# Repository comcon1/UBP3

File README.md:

# Universal Biopotential Amplifier - UBP3

Wideband multichannel differential amplifier with modular design and adjustable analogous commutation.

## Project video

## Technical characteristics

- Input power: -15, 0, +15 V
- Type: differential
- Input resistance: 1 GOhm
- Noise level at connected inputs:
  - < 0.15 mkV (at 0.3-150 Hz)
  - < 0.8 mkV (at 0.3-1000 Hz)
- Gain coefficient:
  - Input cascade: 1, 10
  - Output cascade: 3, 10, 30, 100, 300, 1000
- Filtering:
  - Intensity: 12 dB/octave
  - LowPass: 35, 70, 150, 300, 1000, 2000, 5000, 10000, 20000 Hz 
  - HighPass: 0.1, 0.3, 1, 5, 20, 100, 300 Hz
- Output range: -5V - +5V

# Project structure

The amplifier is composed of two boards: **InputAmp** and **FilterAmp**. 

## InputAmp

Input gain board performs initial commutation of the bipolar signal with reference monopolar input and calibration signal. Next the board amplifies the signal current with 1x/10x gain.

Corresponding directory contains the complete KiCAD project including scheme and PCB.

## FilterAmp

Preamplified signal is then further amplified inside this board and undergo LowPass and HighPass filtration.

Corresponding directory contains the complete KiCAD project including scheme and PCB.

## Calibrator

Calibrator gets 0/+5V input unipolar source and gives 30/300 Hz of 1/0.1 mV square pulse unipolar signal for feeding the amplifier.

Corresponding directory contains the complete KiCAD project including scheme and PCB.

# Arrangement

Boards are designed for further geometrical stacking as shown at the how-to-assembly scheme:

# History

The prototype of this amplifier was firstly used by Ilya Kuzmin and colleagues for recording ECG of rats on a tredban:

- Tarasova OS, Borzykh AA, Kuz'min IV, et al. [Dynamics of heart rate changes in rats following stepwise change of treadmill running speed]. Ross Fiziol Zh Im I M Sechenova. 2012; 98(11):1372-9.

Now it is used by Georgy Nikolaev and his students for recording EEG in the research of audiogenic epilepsy on rat model:

- Fedotova IB, Surina NM, Nikolaev GM, Revishchin AV, Poletaeva II. Rodent Brain Pathology, Audiogenic Epilepsy. Biomedicines. 2021; 9(11):1641. https://doi.org/10.3390/biomedicines9111641

# Licensing 

The project "Universal Biopotential Amplifier" 
(I. Kuzmin @kuzmin-ilya, A. Nesterenko @comcon1, G. Nikolaev)  
is released under  license CC BY-SA 3.0.

Submodules listed as independent projects are not part of this project and 
are released under their own licenses.

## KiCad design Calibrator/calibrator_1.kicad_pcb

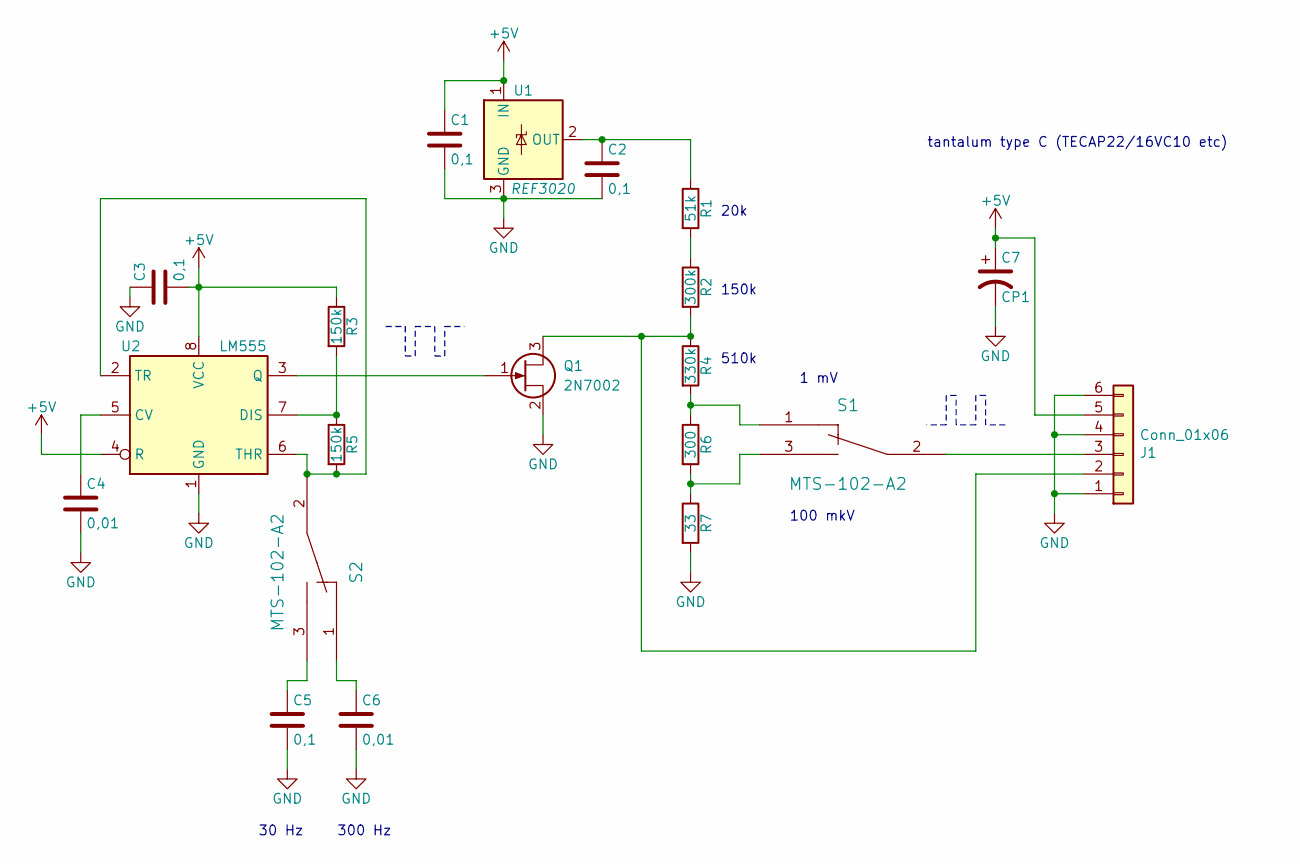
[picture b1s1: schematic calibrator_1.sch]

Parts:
C1, C2, C3, C5: 0,1; C_0805_2012Metric_Pad1.15x1.40mm_HandSolder
C4, C6: 0,01; C_0805_2012Metric_Pad1.15x1.40mm_HandSolder
C7: CP1; CP_EIA-6032-28_Kemet-C_Pad2.25x2.35mm_HandSolder
J1: Conn_01x06; PinHeader_1x06_P2.54mm_Horizontal
Q1: 2N7002; SOT-23_Handsoldering
R1: 51k; R_0805_2012Metric_Pad1.15x1.40mm_HandSolder
R2: 300k; R_0805_2012Metric_Pad1.15x1.40mm_HandSolder
R3, R5: 150k; R_0805_2012Metric_Pad1.15x1.40mm_HandSolder
R4: 330k; R_0805_2012Metric_Pad1.15x1.40mm_HandSolder
R6: 300; R_0805_2012Metric_Pad1.15x1.40mm_HandSolder
R7: 33; R_0805_2012Metric_Pad1.15x1.40mm_HandSolder
S1, S2: MTS-102-A2
U1: REF3020; SOT-23_Handsoldering
U2: LM555; SOIC-8_3.9x4.9mm_P1.27mm

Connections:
+5V: C1.1, C3.2, C7.1, J1.5, R3.1, U1.1 (IN), U2.4 (R), U2.8 (VCC)
GND: C1.2, C2.2, C3.1, C4.2, C5.2, C6.2, C7.2, J1.1, J1.4, J1.6, Q1.2 (S), R7.2, U1.3 (GND), U2.1 (GND)
unnamed: C2.1, R1.1, U1.2 (OUT)
unnamed: C4.1, U2.5 (CV)
unnamed: C5.1, S2.3
unnamed: C6.1, S2.1
unnamed: J1.2, Q1.3 (D), R2.2, R4.1
unnamed: J1.3, S1.2
unnamed: Q1.1 (G), U2.3 (Q)
unnamed: R1.2, R2.1
unnamed: R3.2, R5.1, U2.7 (DIS)
unnamed: R4.2, R6.1, S1.1
unnamed: R5.2, S2.2, U2.2 (TR), U2.6 (THR)
unnamed: R6.2, R7.1, S1.3

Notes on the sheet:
30 Hz
300 Hz
1 mV
100 mkV
tantalum type C (TECAP22/16VC10 etc)
510k
150k
20k

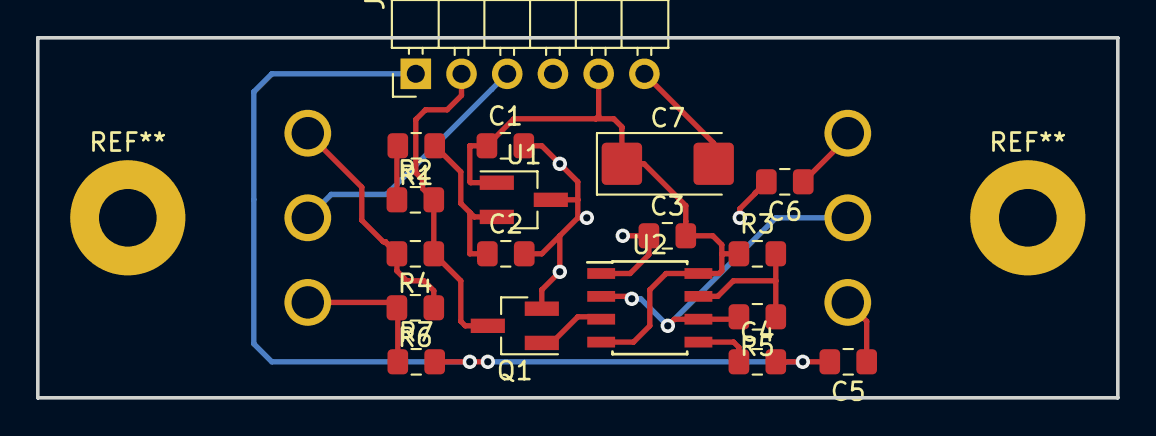
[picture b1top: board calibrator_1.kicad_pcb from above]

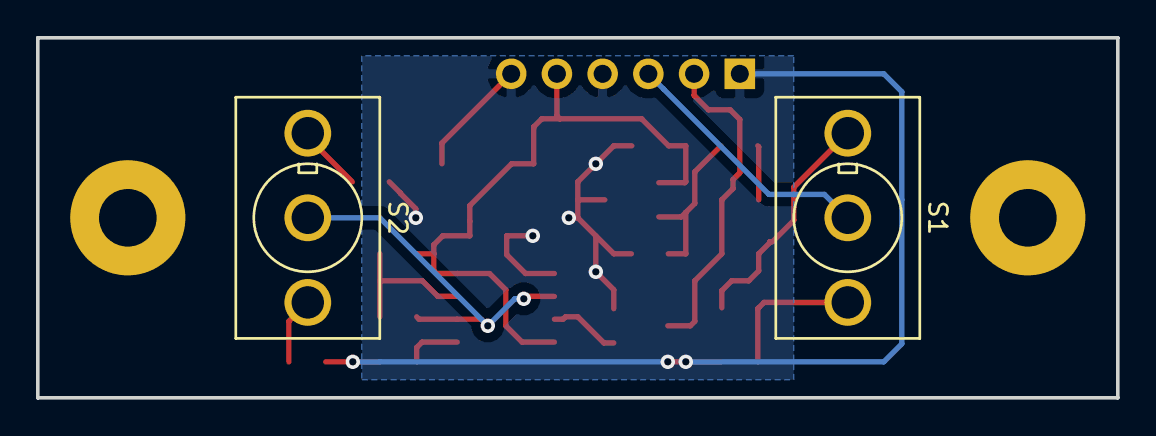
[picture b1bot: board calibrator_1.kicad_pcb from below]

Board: 2 copper layers, 60.0 x 20.0 mm, 20 parts (2 on the bottom side), 14 nets.

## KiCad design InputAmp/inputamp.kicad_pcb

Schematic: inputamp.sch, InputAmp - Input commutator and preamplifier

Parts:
C1, C2, C5: 1,0; C_Rect_L7.5mm_W6.5mm_P5.00mm
C3, C4: 0,1; C_0805_2012Metric_Pad1.18x1.45mm_HandSolder
J1: Conn_01x04; PinHeader_1x04_P2.54mm_Vertical
J2: Conn_01x03; PhoenixContact_MCV_1,5_3-G-3.81_1x03_P3.81mm_Vertical
J3, J5: Conn_01x04; SolderWirePad_1x04_P3.81mm_Drill1.2mm
J4: Conn_01x03; SolderWirePad_1x03_P3.81mm_Drill1.2mm
R1, R2: 20M; R_Axial_DIN0309_L9.0mm_D3.2mm_P12.70mm_Horizontal
R3: 7,5k; R_0805_2012Metric_Pad1.20x1.40mm_HandSolder
R4, R5, R6, R7, R8, R9: 30k; R_0805_2012Metric_Pad1.20x1.40mm_HandSolder
R10: 2M; R_0805_2012Metric_Pad1.20x1.40mm_HandSolder
R11: 33k; R_0805_2012Metric_Pad1.20x1.40mm_HandSolder
R12: 300k; R_0805_2012Metric_Pad1.20x1.40mm_HandSolder
SW1, SW2: MTS-202-A2; MTS-202-A2_odd_even
SW3, SW5, SW6: MTS-102-A2
SW4, SW7: MTS-212-A2; MTS-202-A2_odd_even
U1: TLC2274; SOIC-14_3.9x8.7mm_P1.27mm

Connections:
+5V: C3.2, J1.1, J4.1, U1.4
-5V: C4.2, J1.2, J4.3, U1.11
GND: C3.1, C4.1, J1.4, J2.2, J3.2, J4.2, J5.2, R1.2, R2.2, R8.2, R10.2, R11.2, SW1.5 (C), SW4.5 (C), SW7.6 (C)
unnamed: C1.1, R1.1, SW2.3 (B), U1.3
unnamed: C1.2, SW1.3 (B), SW2.1 (A)
unnamed: C2.1, R2.1, SW2.4 (B), U1.5
unnamed: C2.2, SW1.4 (B), SW2.2 (A)
unnamed: C5.1, R10.1, U1.12
unnamed: C5.2, R9.1, SW3.1, U1.8
unnamed: J1.3, SW3.2
unnamed: J2.1, SW7.2 (A)
unnamed: J2.3, SW4.1 (A)
unnamed: J3.1, J5.1, SW5.3, SW6.3
unnamed: J3.3, J5.3, SW1.6 (C)
unnamed: J3.4, J5.4, SW4.4 (B), SW7.3 (B)
unnamed: R3.1, R4.2, U1.2
unnamed: R3.2, R5.2, U1.6
unnamed: R4.1, R6.2, U1.1
unnamed: R5.1, R7.2, U1.7
unnamed: R6.1, R9.2, U1.9
unnamed: R7.1, R8.1, U1.10
unnamed: R11.1, R12.2, U1.13
unnamed: R12.1, SW3.3, U1.14
unnamed: SW1.1 (A), SW5.2
unnamed: SW1.2 (A), SW6.2
unnamed: SW4.3 (B), SW6.1, SW7.5 (C)
unnamed: SW4.6 (C), SW5.1, SW7.4 (B)

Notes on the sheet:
x10
CAL
ShieldGND
C1, C2, C5 - Epcos B32529C0105K000
Output connector (to "filteramp" block)
Reserve connector to supply power for input devices
Signal input connector
IN- GND IN+
LowPass frequency is about 0.1 Hz
SIG_OUT GND
REF
Rin
CAL_R
"CAL_R": to the +1V output of the calibrator through 1 MOhm "CAL": directly to the +1mV output of the calibrator "REF": when the circuite works in a stack, one of the inputs (called REF) is connected to all boards and may replace + or - inputs "ShieldGND": connect the shield of REF wire and DON'T c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
Connect to J5 of the next board in a stack. DON'T connect ShieldGND between boards!

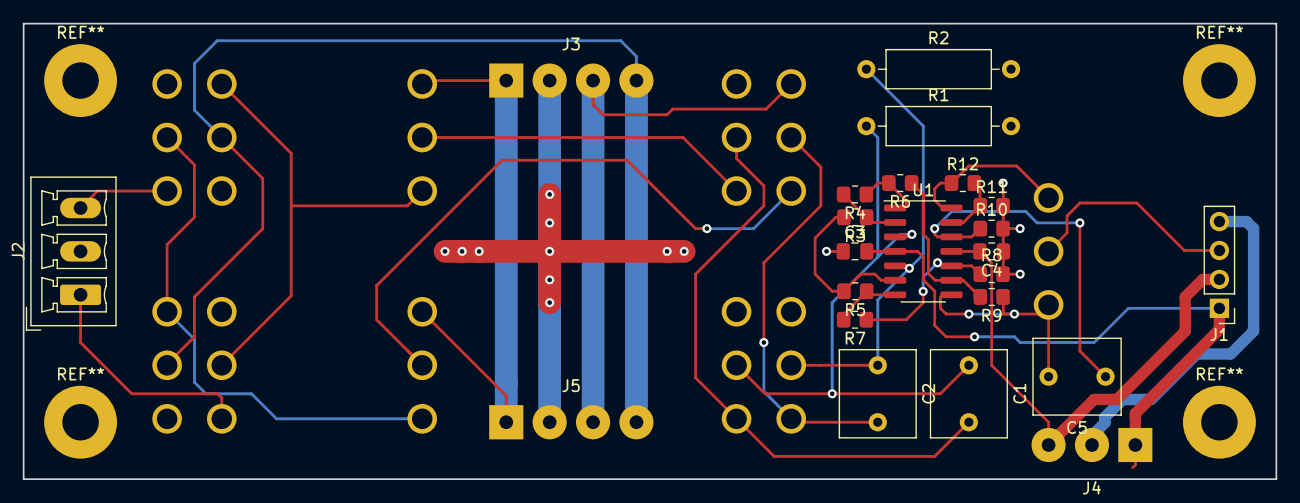
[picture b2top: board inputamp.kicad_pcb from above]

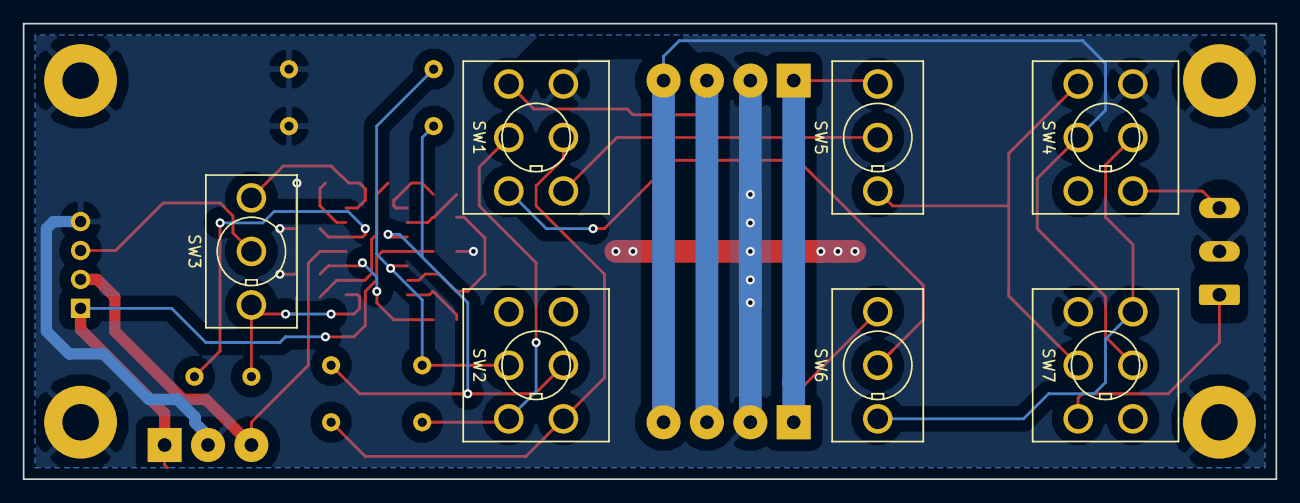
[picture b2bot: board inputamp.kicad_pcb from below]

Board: 2 copper layers, 110.0 x 40.0 mm, 30 parts (7 on the bottom side), 27 nets.

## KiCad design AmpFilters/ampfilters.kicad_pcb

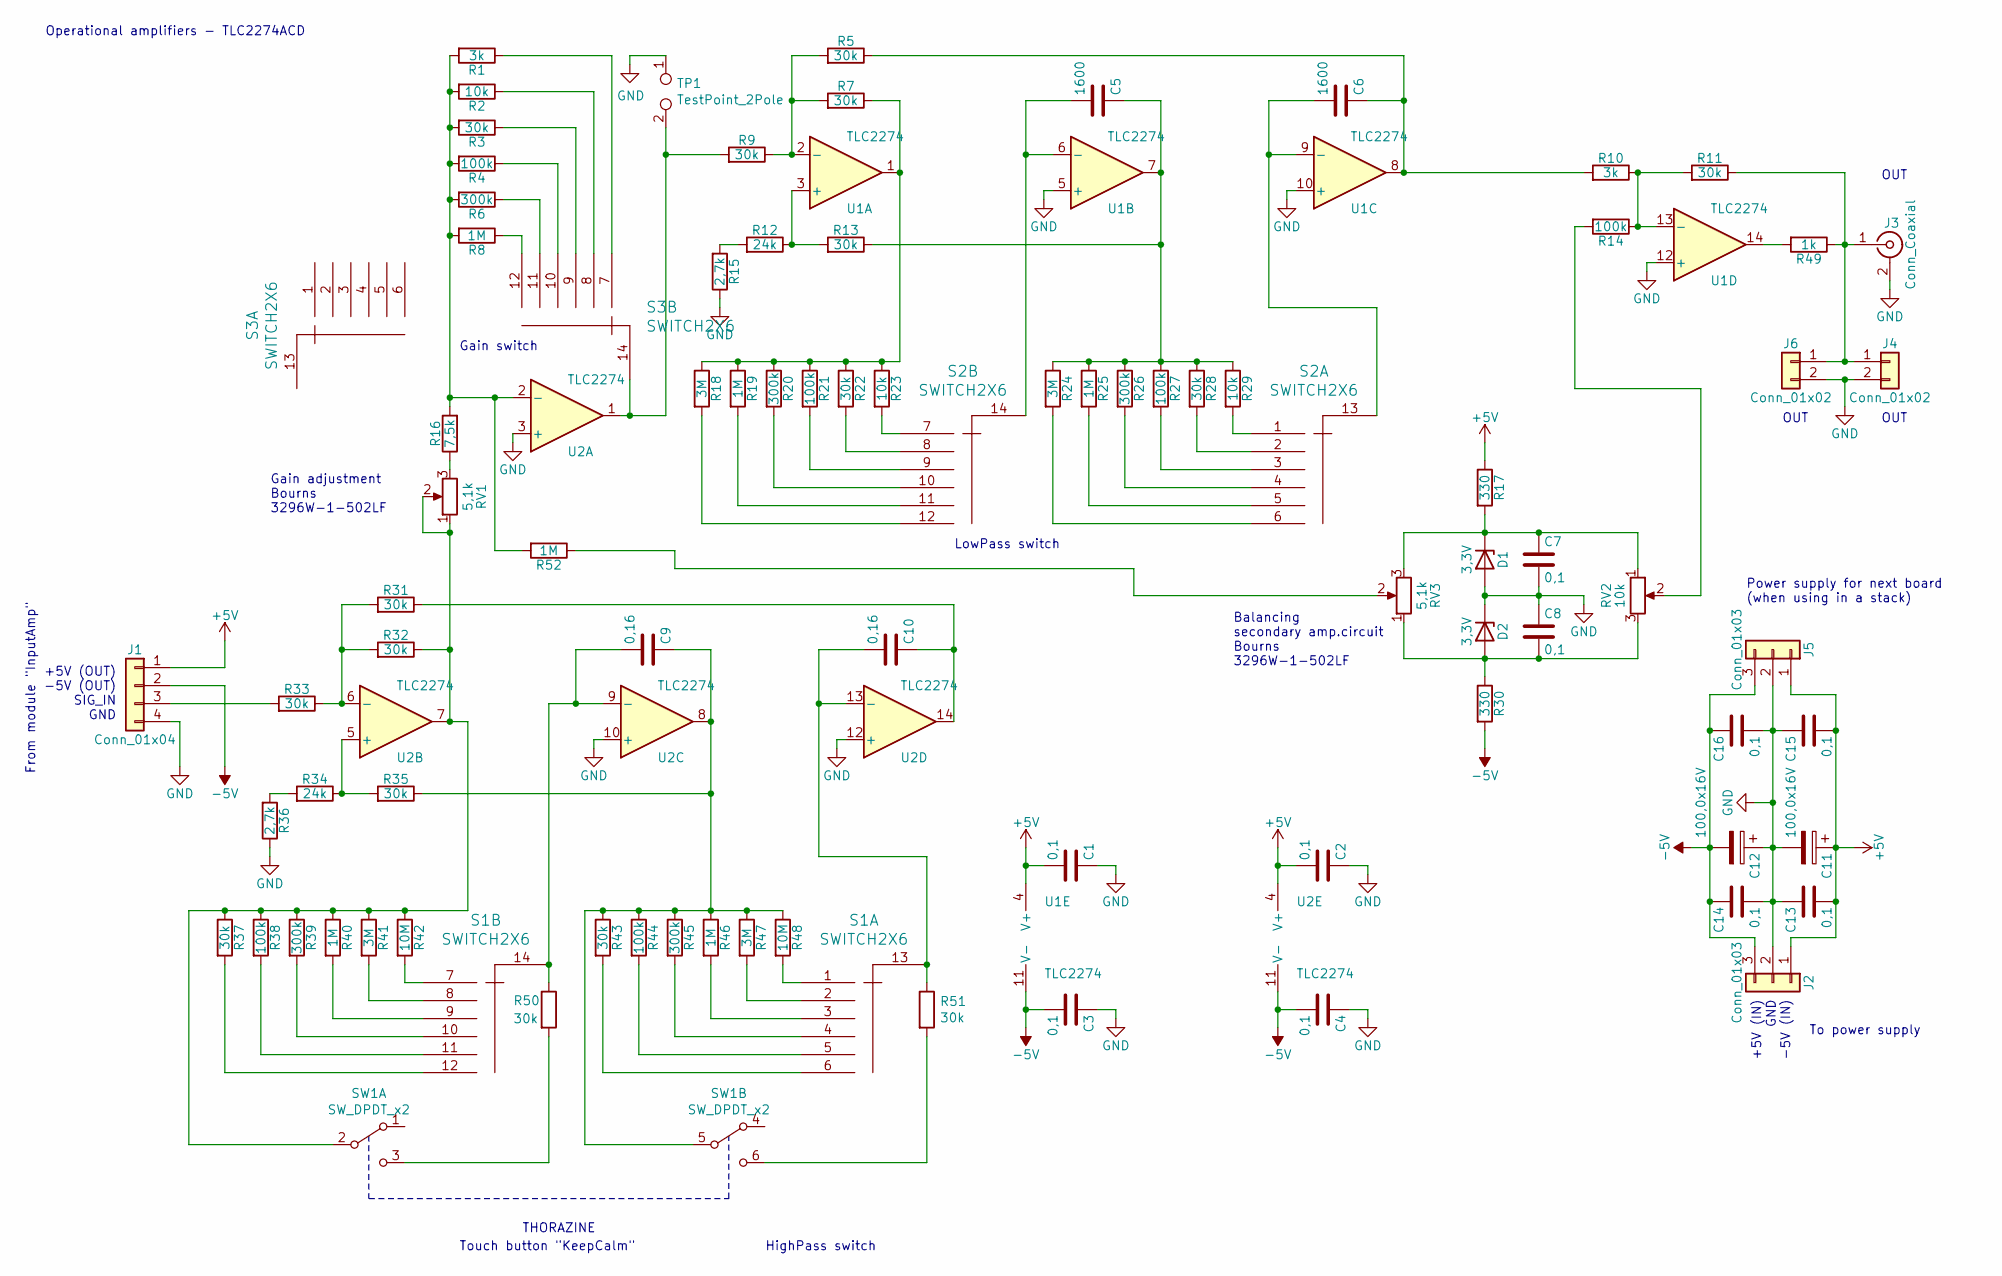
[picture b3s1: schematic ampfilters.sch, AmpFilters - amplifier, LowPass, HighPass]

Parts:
C1, C2, C3, C4, C7, C8, C13, C14, C15, C16: 0,1; C_0805_2012Metric_Pad1.18x1.45mm_HandSolder
C5, C6: 1600; 71-7small
C9, C10: 0,16; 71-7big
C11, C12: 100,0x16V; CP_Radial_D8.0mm_P5.00mm
D1, D2: 3,3V; D_1206_3216Metric_Pad1.42x1.75mm_HandSolder
J1: Conn_01x04; PinHeader_1x04_P2.54mm_Vertical
J2, J5: Conn_01x03; SolderWirePad_1x03_P3.81mm_Drill1.2mm
J3: Conn_Coaxial; BNC-7043
J4, J6: Conn_01x02; SolderWirePad_1x02_P3.81mm_Drill1.2mm
R1, R10: 3k; R_0805_2012Metric_Pad1.20x1.40mm_HandSolder
R2, R23, R29: 10k; R_0805_2012Metric_Pad1.20x1.40mm_HandSolder
R3, R5, R7, R9, R11, R13, R22, R28, R31, R32, R33, R35, R37, R43, R50, R51: 30k; R_0805_2012Metric_Pad1.20x1.40mm_HandSolder
R4, R14, R21, R27, R38, R44: 100k; R_0805_2012Metric_Pad1.20x1.40mm_HandSolder
R6, R20, R26, R39, R45: 300k; R_0805_2012Metric_Pad1.20x1.40mm_HandSolder
R8, R19, R25, R40, R46, R52: 1M; R_0805_2012Metric_Pad1.20x1.40mm_HandSolder
R12, R34: 24k; R_0805_2012Metric_Pad1.20x1.40mm_HandSolder
R15, R36: 2,7k; R_0805_2012Metric_Pad1.20x1.40mm_HandSolder
R16: 7,5k; R_0805_2012Metric_Pad1.20x1.40mm_HandSolder
R17, R30: 330; R_0805_2012Metric_Pad1.20x1.40mm_HandSolder
R18, R24, R41, R47: 3M; R_0805_2012Metric_Pad1.20x1.40mm_HandSolder
R42, R48: 10M; R_0805_2012Metric_Pad1.20x1.40mm_HandSolder
R49: 1k; R_0805_2012Metric_Pad1.20x1.40mm_HandSolder
RV1, RV3: 5,1k; Potentiometer_Bourns_3296W_Vertical
RV2: 10k; POT_VERT
S1, S2, S3: SWITCH2X6; SR25P-1-2-6_mirrored
SW1: SW_DPDT_x2; PS700
TP1: TestPoint_2Pole; PinHeader_1x02_P2.54mm_Vertical
U1, U2: TLC2274; SOIC-14_3.9x8.7mm_P1.27mm

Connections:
+5V: C1.2, C2.2, C11.1, C13.2, C15.2, J1.1, J2.1, J5.1, R17.1, U1.4 (V+), U2.4 (V+)
-5V: C3.2, C4.2, C12.2, C14.1, C16.1, J1.2, J2.3, J5.3, R30.2, U1.11 (V-), U2.11 (V-)
GND: C1.1, C2.1, C3.1, C4.1, C7.2, C8.1, C11.2, C12.1, C13.1, C14.2, C15.1, C16.2, D1.2 (A), D2.1 (K), J1.4, J2.2, J3.2 (Ext), J4.2, J5.2, J6.2, R15.1, R36.1, TP1.1, U1.5 (+), U1.10 (+), U1.12 (+), U2.3 (+), U2.10 (+), U2.12 (+)
unnamed: C5.1, R13.1, R24.1, R25.1, R26.1, R27.1, R28.1, R29.1, U1.7
unnamed: C5.2, S2.14, U1.6 (-)
unnamed: C6.1, R5.1, R10.2, U1.8
unnamed: C6.2, S2.13, U1.9 (-)
unnamed: C7.1, D1.1 (K), R17.2, RV2.1, RV3.3
unnamed: C8.2, D2.2 (A), R30.1, RV2.3, RV3.1
unnamed: C9.1, R35.1, R43.1, R44.1, R45.1, R46.1, R47.1, R48.1, SW1.5 (B), U2.8
unnamed: C10.1, R31.1, U2.14
unnamed: J1.3, R33.2
unnamed: J3.1 (In), J4.1, J6.1, R11.1, R49.1
unnamed: R1.1, S3.7
unnamed: R1.2, R2.2, R3.2, R4.2, R6.2, R8.2, R16.2, R52.2, U2.2 (-)
unnamed: R2.1, S3.8
unnamed: R3.1, S3.9
unnamed: R4.1, S3.10
unnamed: R5.2, R7.2, R9.1, U1.2 (-)
unnamed: R6.1, S3.11
unnamed: R8.1, S3.12
unnamed: R9.2, S3.14, TP1.2, U2.1
unnamed: R10.1, R11.2, R14.1, U1.13 (-)
unnamed: R12.1, R13.2, U1.3 (+)
unnamed: R12.2, R15.2
unnamed: R14.2, RV2.2
unnamed: R16.1, RV1.3
unnamed: R7.1, R18.1, R19.1, R20.1, R21.1, R22.1, R23.1, U1.1
unnamed: R18.2, S2.12
unnamed: R19.2, S2.11
unnamed: R20.2, S2.10
unnamed: R21.2, S2.9
unnamed: R22.2, S2.8
unnamed: R23.2, S2.7
unnamed: R24.2, S2.6
unnamed: R25.2, S2.5
unnamed: R26.2, S2.4
unnamed: R27.2, S2.3
unnamed: R28.2, S2.2
unnamed: R29.2, S2.1
unnamed: R31.2, R32.2, R33.1, U2.6 (-)
unnamed: R32.1, R37.1, R38.1, R39.1, R40.1, R41.1, R42.1, RV1.1, RV1.2, SW1.2 (B), U2.7
unnamed: R34.1, R35.2, U2.5 (+)
unnamed: R34.2, R36.2
unnamed: R37.2, S1.12
unnamed: R38.2, S1.11
unnamed: R39.2, S1.10
unnamed: R40.2, S1.9
unnamed: R41.2, S1.8
unnamed: R42.2, S1.7
unnamed: R43.2, S1.6
unnamed: R44.2, S1.5
unnamed: R45.2, S1.4
unnamed: R46.2, S1.3
unnamed: R47.2, S1.2
unnamed: R48.2, S1.1
unnamed: R49.2, U1.14
unnamed: R50.2, SW1.3 (C)
unnamed: R51.2, SW1.6 (C)
unnamed: R52.1, RV3.2

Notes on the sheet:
THORAZINE
Gain adjustment Bourns 3296W-1-502LF
OUT
Balancing secondary amp.circuit Bourns 3296W-1-502LF
Gain switch
+5V (IN) GND -5V (IN)
+5V (OUT) -5V (OUT) SIG_IN GND
Touch button "KeepCalm"
From module "InputAmp"
To power supply
Operational amplifiers - TLC2274ACD
HighPass switch
LowPass switch
Power supply for next board (when using in a stack)

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
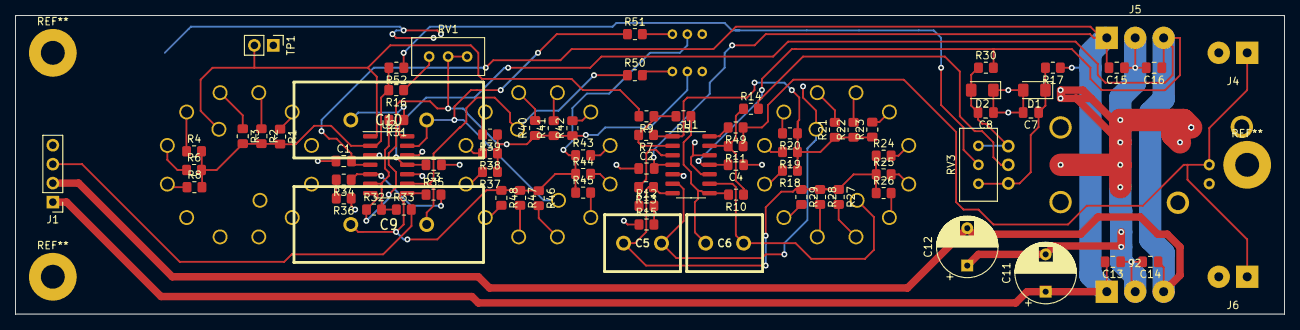
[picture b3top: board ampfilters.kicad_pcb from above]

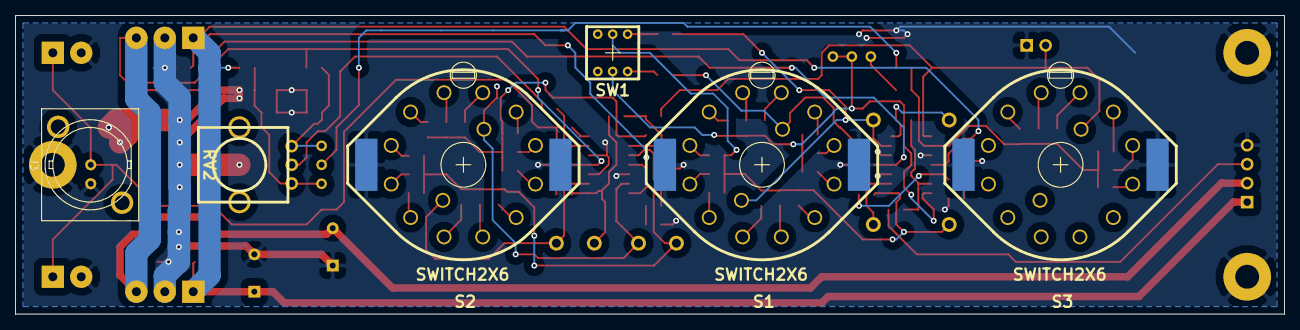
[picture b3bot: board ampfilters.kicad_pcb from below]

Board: 2 copper layers, 170.0 x 40.0 mm, 86 parts (6 on the bottom side), 62 nets.

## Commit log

2022-10-26 firstly add main circuits and associated files
2022-10-26 initial README update
2022-10-28 add kikad libs submodules
2022-10-28 Add Calibrator board to the project
2022-11-25 insert video from GOSH and history to README
